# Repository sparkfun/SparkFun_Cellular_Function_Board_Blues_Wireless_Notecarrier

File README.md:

SparkFun MicroMod Cellular Function Board - Blues Wireless Notecarrier
===========================================================

[*SparkFun MicroMod Cellular Function Board - Blues Wireless Notecarrier (WRL-20409)*](https://www.sparkfun.com/products/20409)

A MicroMod Function Board that works as a Blues Wireless Notecarrier featuring the Notecard - NOTE-NBGL-500. This Function Board adds a cellular module to the MicroMod ecosystem allowing users to send and receive data from anywhere with a compatible cellular signal. The Notecard has a built-in SIM card and includes a 10 year subscription and 500MB of data included in the price. An onboard nano SIM slot is provided for users who prefer or need to use their own SIM. The Notecard module also comes with integrated cellular, SIM, onboard GPS, 3-axis accelerometer with an on-chip temperature sensor. On top of that, the Notecard features outboard device firmware updates (DFU) meaning you can reprogram a connected Processor remotely through Blues' Notehub service! There are some limitations to this process so make sure to read through the Outboard documentation in the SparkFun Hookup Guide for more information on how to properly perform Outboard device firmware updates. 

Repository Contents
-------------------

* **/Firmware/examples**
* **/Hardware**

Documentation
-------------

* **[Hookup Guide](https://learn.sparkfun.com/tutorials/cellular-function-board---blues-wireless-notecarrier)** - A standard Hookup Guide to get started with the MicroMod Cellular Function Board - Blues Wireless Notecarrier.

Product Versions
----------------

* [WRL-20409](https://www.sparkfun.com/products/20409) - Initial Release

Version History
---------------

* v1.0 - Initial release

License Information
-------------------

This product is _**open source**_! 

Please review the LICENSE.md file for license information. 

If you have any questions or concerns on licensing, please contact technical support on our [SparkFun forums](https://forum.sparkfun.com/viewforum.php?f=152).

Distributed as-is; no warranty is given.

- Your friends at SparkFun.

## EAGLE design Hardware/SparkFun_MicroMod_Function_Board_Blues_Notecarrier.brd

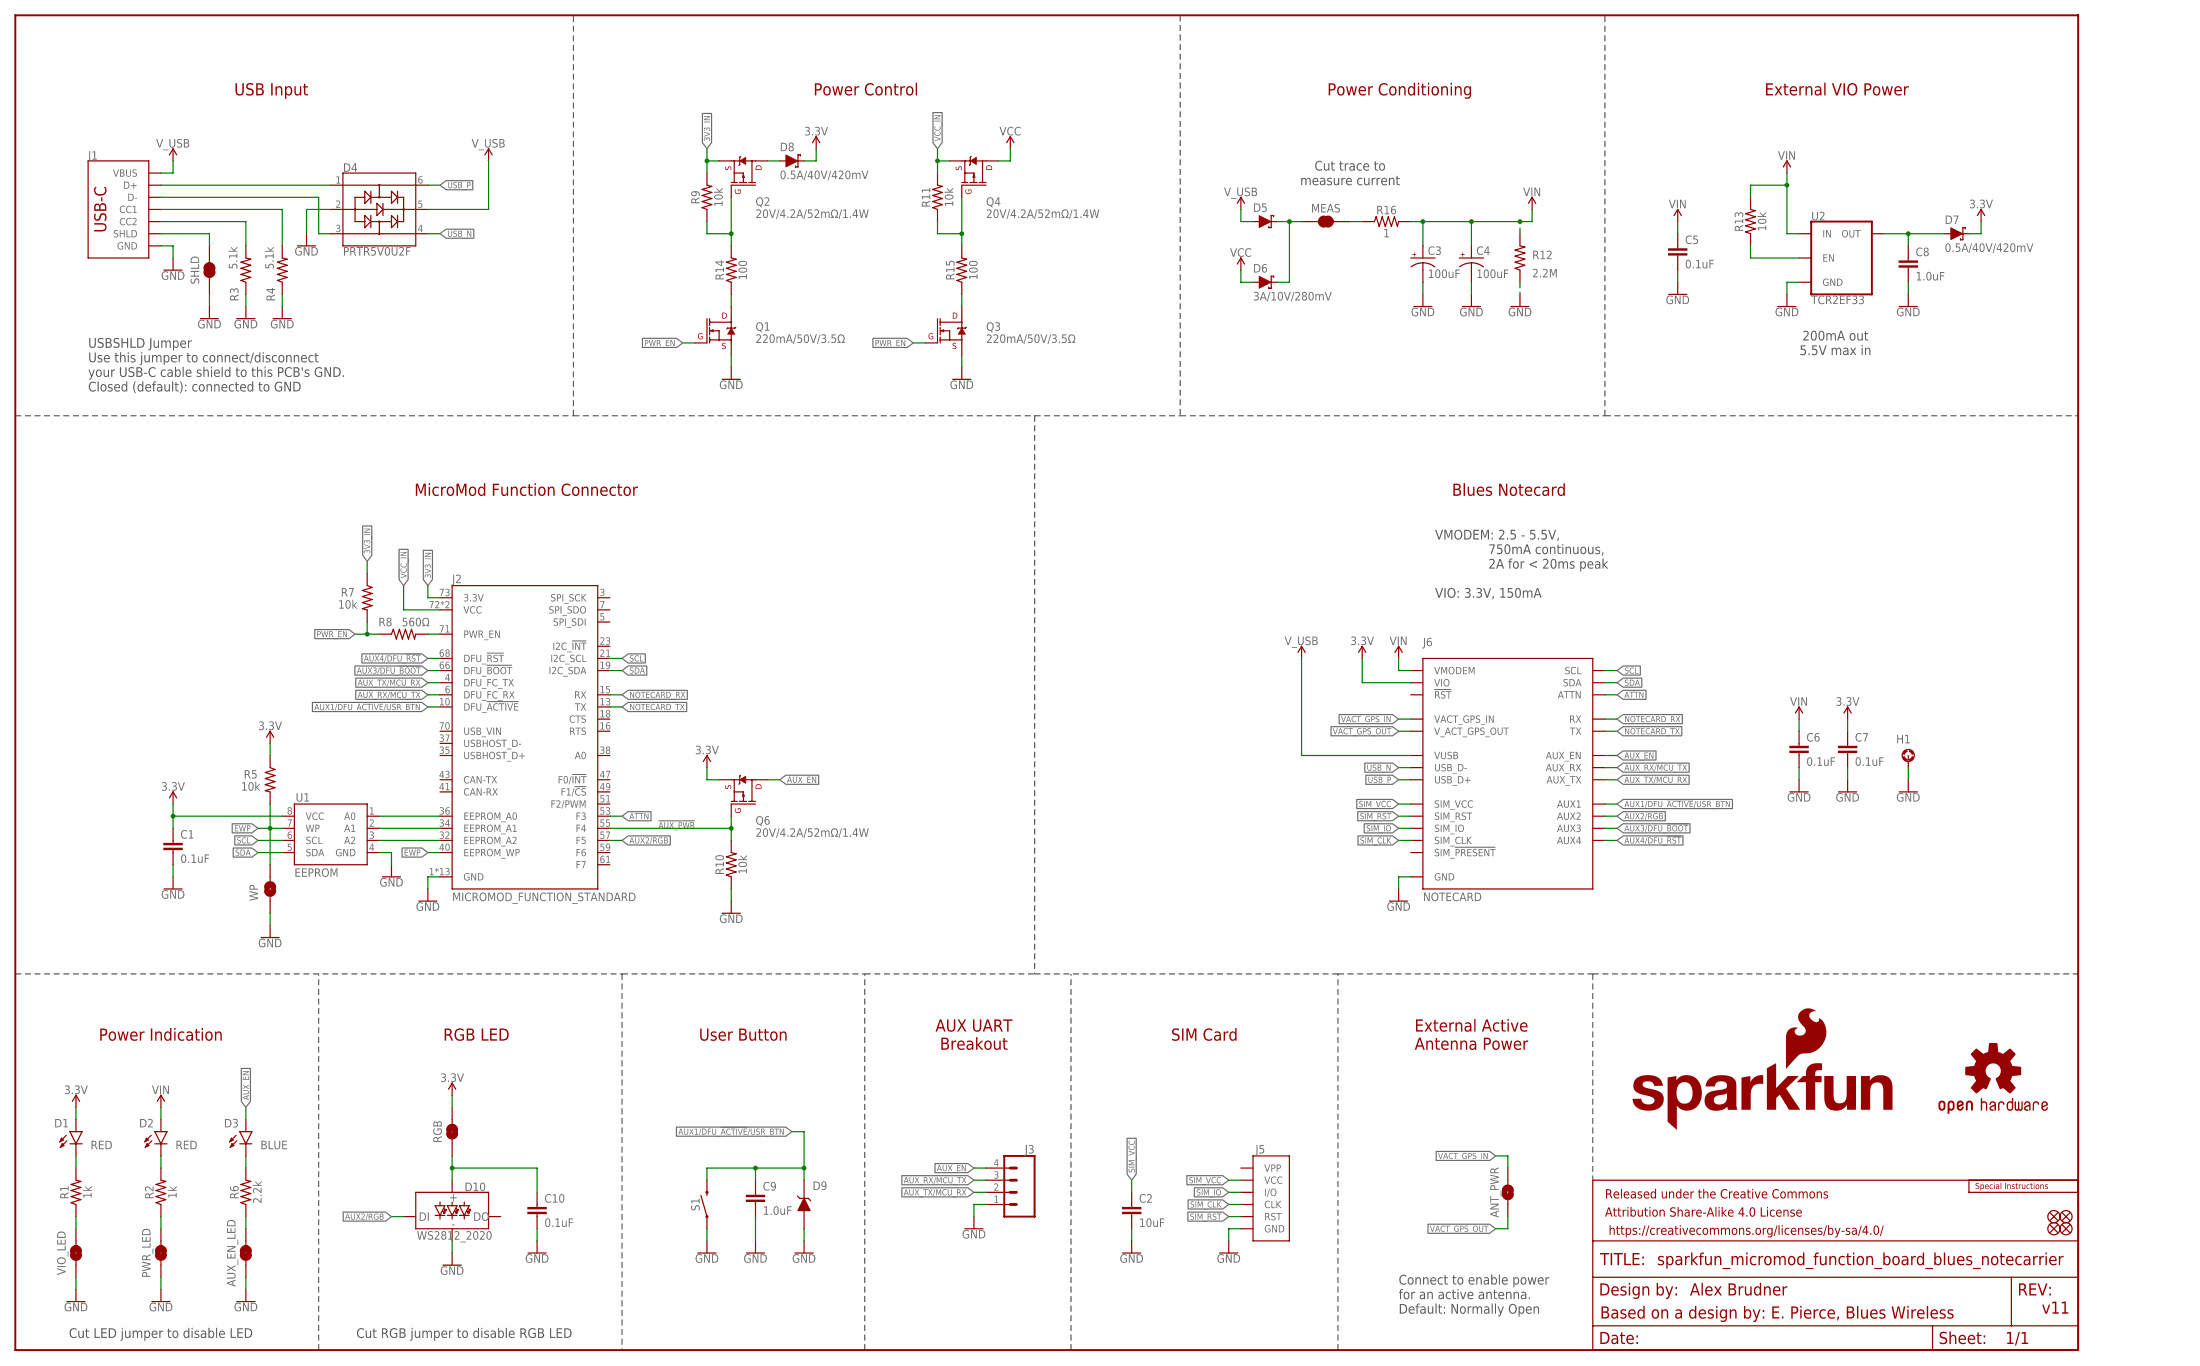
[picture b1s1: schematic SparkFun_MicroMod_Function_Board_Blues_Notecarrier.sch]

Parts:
ANT_PWR: JUMPER-SMT_2_NO_SILK; SMT-JUMPER_2_NO_SILK
AUX_EN_LED: JUMPER-SMT_2_NC_TRACE_SILK; SMT-JUMPER_2_NC_TRACE_SILK
C1, C5, C6, C7, C10: 0.1uF; 0402-TIGHT
C2: 10uF; 0805
C3, C4: 100uF; PANASONIC_D
C8, C9: 1.0uF; 0402-TIGHT
D1, D2: RED; LED-0603
D3: BLUE; LED-0603
D4: PRTR5V0U2F; SOT886
D5, D6: 3A/10V/280mV; SOD-323
D7, D8: 0.5A/40V/420mV; SOD-323
D9: SMBJP6KE6.8A-TP; DO-214AA
D10: WS2812_2020; WS2812-2020
FD1, FD2, FD3, FD4: FIDUCIALUFIDUCIAL; FIDUCIAL-MICRO
FRAME1: FRAME-LEDGER; CREATIVE_COMMONS
H1: STAND-OFF-REFLOW-M2.5_2.5MM_TALL; STAND-OFF-REFLOW-M2.5
J1: USB_C_2-LAYER_PADS; USB-C-16P-2LAYER-PADS
J2: MICROMOD_FUNCTION_STANDARD; M.2-CARD-E-22_FUNCTION_STANDARD
J3: CONN_041X04_NO_SILK_NO_POP; 1X04_NO_SILK
J5: SIMHOLDER-NANOSIM-MOLEX; NANO_SIM_MOLEX_104224-0820
J6: NOTECARD; M.2-CONNECTOR-E
LOGO1: SFE_LOGO_NAME_FLAME.1_INCH; SFE_LOGO_NAME_FLAME_.1
LOGO2: SPECIAL_INSTRUCTIONS-ORDERING; ORDERING_INSTRUCTIONS
LOGO3: OSHW-LOGOMINI; OSHW-LOGO-MINI
MEAS: JUMPER-COMBO_2_NC_TRACE; COMBO-JUMPER_2_NC_TRACE
PWR_LED: JUMPER-SMT_2_NC_TRACE_SILK; SMT-JUMPER_2_NC_TRACE_SILK
Q1, Q3: 220mA/50V/3.5Ω; SOT23-3
Q2, Q4, Q6: 20V/4.2A/52mΩ/1.4W; SOT23-3
R1, R2: 1k; 0402-TIGHT
R3, R4: 5.1k; 0402-TIGHT
R5, R7, R9, R10, R11, R13: 10k; 0402-TIGHT
R6: 2.2k; 0402-TIGHT
R8: 560Ω; 0402-TIGHT
R12: 2.2M; 0402-TIGHT
R14, R15: 100; 0402-TIGHT
R16: 1; 0603
RGB: JUMPER-SMT_2_NC_TRACE_SILK; SMT-JUMPER_2_NC_TRACE_SILK
S1: MOMENTARY-SWITCH-SPST-SMD-4.6X2.8MM; TACTILE_SWITCH_SMD_4.6X2.8MM
SHLD: JUMPER-SMT_2_NC_TRACE_SILK; SMT-JUMPER_2_NC_TRACE_SILK
U1: EEPROM; SO08
U2: TCR2EF33; SOT23-5
VIO_LED: JUMPER-SMT_2_NC_TRACE_SILK; SMT-JUMPER_2_NC_TRACE_SILK
WP: JUMPER-SMT_2_NO_SILK; SMT-JUMPER_2_NO_SILK

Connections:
3.3V: C1.1, C7.1, D1.A, D7.C, D8.C, J6.2 (VIO), J6.4 (VIO), Q6.2 (S), R5.1, RGB.2, U1.8 (VCC)
3V3_IN: J2.73 (3.3V), Q2.2 (S), R7.1, R9.2
!AUX_PWR!: J2.55 (F4), Q6.1 (G), R10.2
A0: J2.36 (EEPROM_A0), U1.1 (A0)
A1: J2.34 (EEPROM_A1), U1.2 (A1)
A2: J2.32 (EEPROM_A2), U1.3 (A2)
ATTN: J2.53 (F3), J6.54 (ATTN)
AUX1/DFU_!ACTIVE!/USR_BTN: C9.1, D9.C, J2.10 (DFU_!ACTIVE!), J6.46 (AUX1), S1.3 (2), S1.4 (2)
AUX2/RGB: D10.DI, J2.57 (F5), J6.48 (AUX2)
AUX3/DFU_!BOOT!: J2.66 (DFU_!BOOT!), J6.50 (AUX3)
AUX4/DFU_!RST!: J2.68 (DFU_!RST!), J6.52 (AUX4)
AUX_EN: D3.A, J3.4, J6.56 (AUX_EN), Q6.3 (D)
AUX_RX/MCU_TX: J2.6 (DFU_FC_RX), J3.3, J6.58 (AUX_RX)
AUX_TX/MCU_RX: J2.4 (DFU_FC_TX), J3.2, J6.60 (AUX_TX)
EWP: J2.40 (EEPROM_WP), R5.2, U1.7 (WP), WP.2
GND: AUX_EN_LED.1, C1.2, C2.2, C3.-, C4.-, C5.2, C6.2, C7.2, C8.2, C9.2, C10.2, D4.2, D9.A, D10.GND, H1.1, J1.GND, J1.GND2 (GND), J2.1 (GND), J2.2 (GND), J2.8 (GND), J2.33 (GND), J2.39 (GND), J2.45 (GND), J2.75 (GND), J2.GND1 (GND), J2.GND2 (GND), J2.GND3 (GND), J2.GND4 (GND), J2.GND5 (GND), J2.GND6 (GND), J3.1, J5.G1 (GND), J5.G2 (GND), J5.G3 (GND), J5.G4 (GND), J5.S4 (GND), J6.3 (GND), J6.5 (GND), J6.6 (GND), J6.11 (GND), J6.18 (GND), J6.33 (GND), J6.39 (GND), J6.45 (GND), J6.51 (GND), J6.57 (GND), J6.71 (GND), J6.73 (GND), PWR_LED.1, Q1.2 (S), Q3.2 (S), R3.1, R4.1, R10.1, R12.1, S1.1, S1.2 (1), SHLD.1, U1.4 (GND), U2.2 (GND), VIO_LED.1, WP.1
unnamed: J2.71 (PWR_EN), R8.2
unnamed: Q2.1 (G), R9.1, R14.2
unnamed: Q4.1 (G), R11.1, R15.2
unnamed: D1.C, R1.2
unnamed: R13.1, U2.3 (EN)
unnamed: D2.C, R2.2
unnamed: D8.A, Q2.3 (D)
unnamed: J1.B5 (CC2), R3.2
unnamed: J1.A5 (CC1), R4.2
unnamed: C8.1, D7.A, U2.5 (OUT)
unnamed: PWR_LED.2, R2.1
unnamed: R1.1, VIO_LED.2
unnamed: D3.C, R6.2
unnamed: AUX_EN_LED.2, R6.1
unnamed: Q1.3 (D), R14.1
unnamed: Q3.3 (D), R15.1
unnamed: MEAS.2, MEAS.4 (2), R16.1
unnamed: C10.1, D10.VCC, RGB.1
unnamed: D5.C, D6.C, MEAS.1, MEAS.3 (1)
NOTECARD_RX: J2.15 (RX), J6.62 (RX)
NOTECARD_TX: J2.13 (TX), J6.64 (TX)
PWR_EN: Q1.1 (G), Q3.1 (G), R7.2, R8.1
SCL: J2.21 (I2C_SCL), J6.40 (SCL), U1.6 (SCL)
SDA: J2.19 (I2C_SDA), J6.42 (SDA), U1.5 (SDA)
SHLD: J1.SHLD1 (SHLD), J1.SHLD2 (SHLD), J1.SHLD3 (SHLD), J1.SHLD4 (SHLD), SHLD.2
SIM_CLK: J5.S3 (CLK), J6.14 (SIM_CLK)
SIM_IO: J5.S6 (I/O), J6.12 (SIM_IO)
SIM_RST: J5.S2 (RST), J6.10 (SIM_RST)
SIM_VCC: C2.1, J5.S1 (VCC), J6.8 (SIM_VCC)
USB_IN_N: D4.3, J1.A7 (D-), J1.B7 (D-)
USB_IN_P: D4.1, J1.A6 (D+), J1.B6 (D+)
USB_N: D4.4, J6.9 (USB_D-)
USB_P: D4.6, J6.7 (USB_D+)
VACT_GPS_IN: ANT_PWR.2, J6.22 (VACT_GPS_IN)
VACT_GPS_OUT: ANT_PWR.1, J6.20 (V_ACT_GPS_OUT)
VCC: D6.A, Q4.3 (D)
VCC_IN: J2.72 (VCC), J2.74 (VCC), Q4.2 (S), R11.2
VIN: C3.+, C4.+, C5.1, C6.1, D2.A, J6.70 (VMODEM), J6.72 (VMODEM), J6.74 (VMODEM), R12.2, R13.2, R16.2, U2.1 (IN)
V_USB: D4.5, D5.A, J1.VBUS1 (VBUS), J1.VBUS2 (VBUS), J6.13 (VUSB)

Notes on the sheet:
Alex Brudner
Based on a design by: E. Pierce, Blues Wireless
v11
MicroMod Function Connector
Power Control
USB Input
Power Conditioning
Blues Notecard
Power Indication
User Button
AUX UART Breakout
SIM Card
External Active Antenna Power
External VIO Power
200mA out 5.5V max in
VMODEM: 2.5 - 5.5V, 750mA continuous, 2A for < 20ms peak VIO: 3.3V, 150mA
USBSHLD Jumper Use this jumper to connect/disconnect your USB-C cable shield to this PCB's GND. Closed (default): connected to GND
Cut LED jumper to disable LED
Cut trace to measure current
Connect to enable power for an active antenna. Default: Normally Open
RGB LED
Cut RGB jumper to disable RGB LED

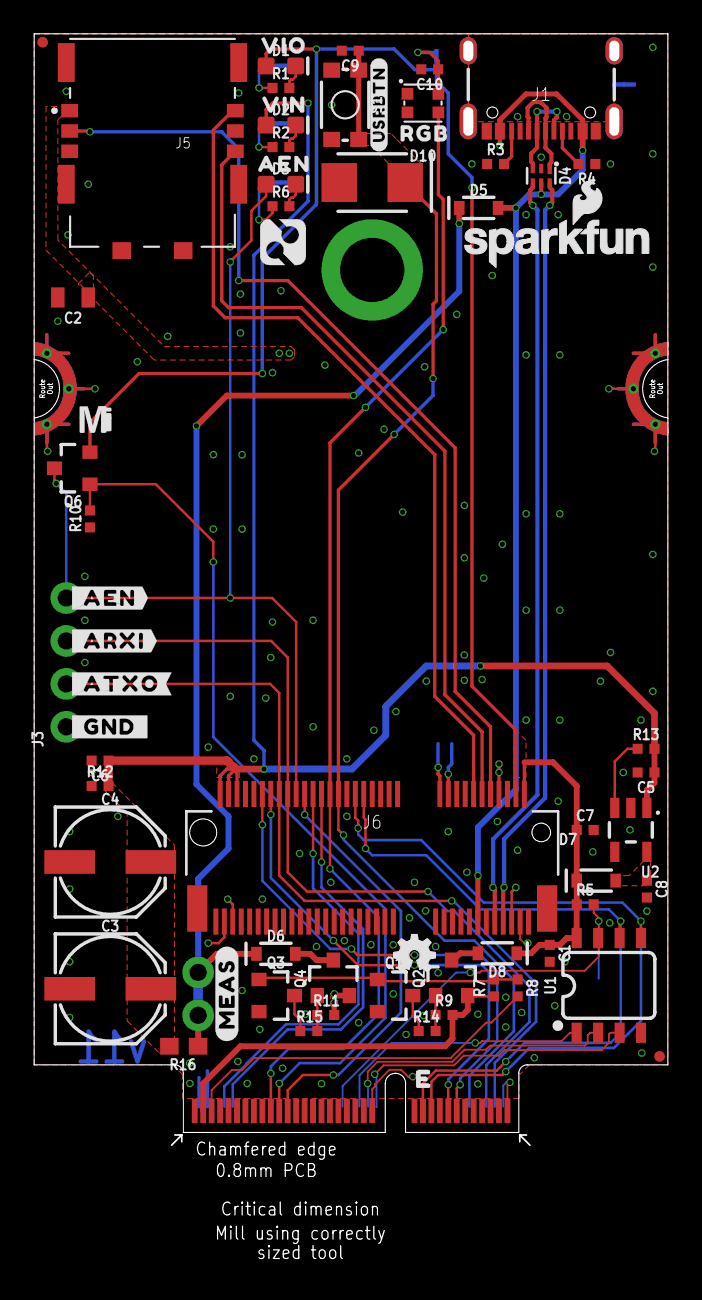
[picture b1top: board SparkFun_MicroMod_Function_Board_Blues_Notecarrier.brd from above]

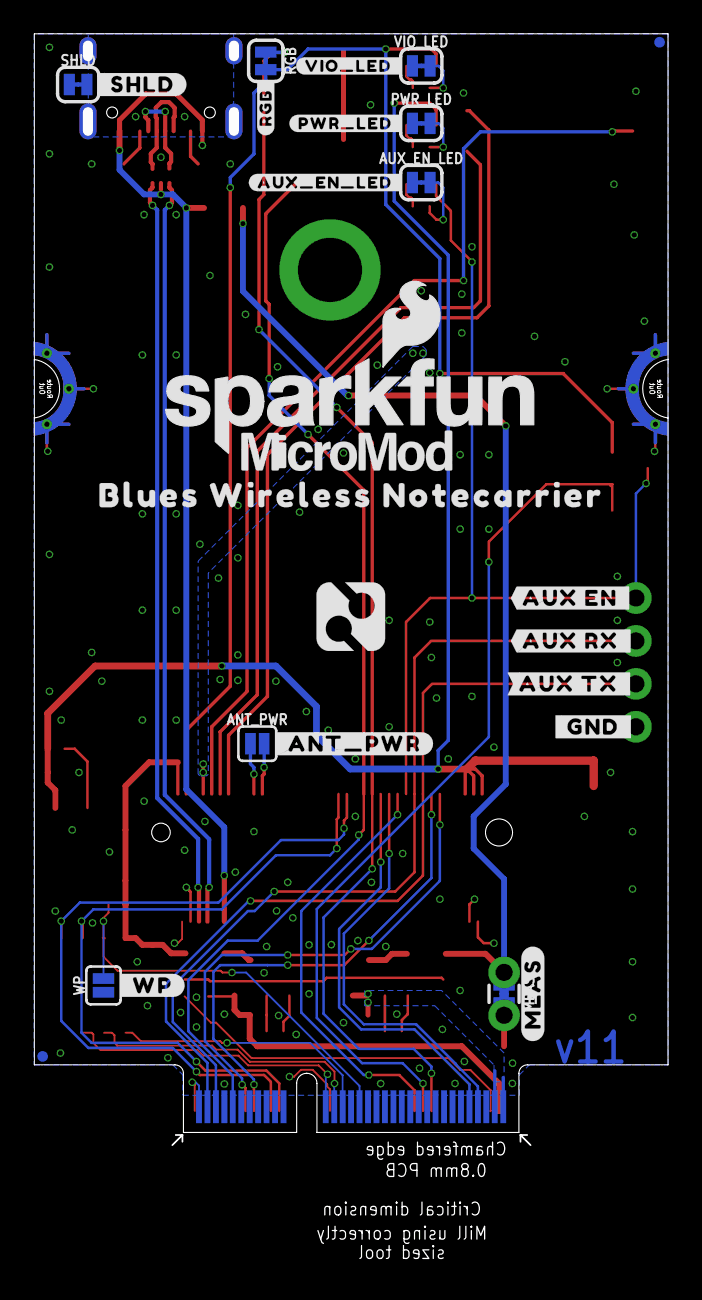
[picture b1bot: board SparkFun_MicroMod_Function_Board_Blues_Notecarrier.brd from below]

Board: 2 copper layers, 37.5 x 65.8 mm, 95 parts (26 on the bottom side), 55 nets.

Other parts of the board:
U$1: AEN1
U$2: VIN3
U$3: VIO4
U$4: #VIO_LED_#21
U$5: #_ARXI#0
U$6: SFE_LOGO_FLAME_STOP_.1
U$7: #_GND_#0
U$8: #_WP#2
U$9: BLUES_WIRELESS_NOTECARRIER0
U$10: NOTEHUB_BLUES#SVG7
U$11: #_ATXO#0
U$12: #AUX_TX_#0
U$13: #_AEN#0
U$14: SFE_LOGO_NAME_FLAME_.2
U$15: #AUX_RX_#0
U$16, U$17: #MEAS#4
U$18: #_ANT_PWR#5
U$19: #AUX_EN_LED_#20
U$20: #_SHLD#23
U$21: #PWR_LED_#17
U$22: #_GND_#24
U$23: NOTEHUB_BLUES#SVG5
U$24: #RGB_#0
U$25: #USRBTN#0
U$26: RGB0
U$29: MICROMOD_MI_LOGO_.35
U$30: #AUX_EN_#0
U$31: MICROMOD_LOGO_.5

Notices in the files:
parts and their libraries:
SparkFun-Aesthetics: Licensing: Creative Commons ShareAlike 4.0 International - https://creativecommons.org/licenses/by-sa/4.0
SparkFun-Aesthetics: Released under the Creative Commons Attribution Share-Alike 4.0 License
SparkFun-Aesthetics: https://creativecommons.org/licenses/by-sa/4.0
